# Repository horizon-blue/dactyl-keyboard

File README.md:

# Dactyl Manuform + Trackball with Ergodox layout (sort of)

Disclaimer: I hacked the script for my own use and hard-coded a bunch of meshes. There's no guarantee that the script will work with another layout.

This repo contains yet another fork of Dactyl Manuform that combines [Loligagger's Dactyl Manuform with Ergodox's layout](https://geekhack.org/index.php?topic=88576.msg2852310#msg2852310) with [Wylderbuild's trakball thumb cluster](https://github.com/bullwinkle3000/dactyl-keyboard)

## Changes

- Comparing to the classical Dactyl Manuform model, the "Ergodox layout" has an additional inner column with three keys on each side
- Fixed the strange artifacts that's on the bottom right of Wylderbuild's trakball thumb cluster connector.

- The 1.5U keycaps used to be hanging beyond the case but this should be fixed now.

Pregenerated STL files can be found in the [things](things/) directory

# Wylderbuilds Dactyl Manuform - Python 3 - Cadquery
So, THIS is a fork of a fork of a fork of a... You get the idea.

This one is a direct fork of [joshreve's brilliant adaptation](https://github.com/joshreve/dactyl-keyboard)  of the original Clojure-based dactyl manuform generator redone in Python 3.
Without his work, none of this would have been nearly as easy and straightforward as it has been.  Vast kudos and thanks to him.

This repo is what I've customized and use to generate the models for the prints I sell online at Wylderbuilds, my Etsy store.

## Main Differences and How to Make it Go
Eventually, joshreve and I hope to merge our changes together, but until then, here's a quick rundown on the current changes.

* Wylderbuilds Trackball cluster -- A new, low-rider Trackball cluster. ("thumb_style": "TRACKBALL_WILD")
* Wylderbuilds BTU Trackball cluster -- An even newer Trackball cluster with ball transfer unit support. ("thumb_style": TRACKBALL_BTU")
* 1.5u pinky column support -- Outside 1.5u pinky columns can be generated ("pinky_1_5U": true, "first_1_5U_row": x, "last_1_5U_row": y)
* Full bottom rows -- Default manuforms drop the bottom row keys on outside columns, this keeps them ("full_last_rows": true)
* Clusters broken out into their own classes -- Making it easier to swap among them and add more.
* Updated Kailh Hot swap holder -- If enabled, the hot swap holder is full size and stronger.
* Cadquery builds generate STLs in addition to STEP files -- The bottom plates are (still) only generated properly when the "ENGINE": "cadquery" is set and this will now generate ready-to-print STLs (some models might need a little repair)
* OTHER MISC BITS: OLED mount wall tweaks, tweaks to screw-sizes and some wall placements, manuform angle and heights tweaked, support for an "overrides" json config file.

The main script has been reworked into a single make_dactyl() function.

The setup and run instructions are still more-or-less the same, but here's some tips:

* The docker file likely won't get far, it hasn't been maintained or updated in some time.

* To run locally, the best route is to install Anaconda or Miniconda, start a conda shell and run the "conda.sh" script.  If you're on Windows and don't want to do the WSL Linux thing, you can do the following:

1. Do the Anaconda/Miniconda bit, above.
2. In a conda shell, run the following lines:

        conda create --name=dactyl-keyboard python=3.7 -y

        conda activate dactyl-keyboard

        conda install -c conda-forge -c cadquery cadquery=2 -y

        pip install dataclasses-json numpy scipy solidpython

        conda update --all -y

Then, still in the shell, navigate to the src directory under the repository root and run:

    python dactyl_manuform.py

This will churn and pump out models into the "things" directory.  In run_config.json, "ENGINE": "solid" or "cadquery" will specify OpenSCAD or STEP/STL files, respectively.  Note that the cadquery option takes considerably longer.  Openscad is best for fast iteration.

I'll update more here as things develop.

# The Dactyl-ManuForm Keyboard - Python 3 - Cadquery
This is a fork of [Dactyl-Manuform](https://github.com/tshort/dactyl-keyboard) by Tom Short, which itself is a fork of [Dactyl](https://github.com/adereth/dactyl-keyboard) by Matthew Adereth, a parameterized, split-hand, concave, columnar, ergonomic keyboard.

While the code structure remains comparable to the original, Clojure and OpenSCAD have been replaced by Python and cadquery/OpenCASCADE.  The predecessors were exceptional contributions to the ergo keyboard community by the authors but used a rather esoteric programming language, Clojure, and a relatively inconsistent geometry engine, OpenSCAD.  My hope is that by converting the code the community will have an easier time modifying and evolving this design.  

## Collaborations and Donations
I decided to start accepting donations to help offset some of the prototyping costs and development time.  There are 2 ways to contribute to this project:

### Purchase a kit or keyboard from https://www.ergohaven.xyz/
I am also supported by [ergohaven](https://www.ergohaven.xyz/).  The Dactyl-Manuforms are generated from this repository.  After working with the owner on additions to support new features we decided to collaborate to evolve the designs they can offer and to support my work.  

### Donate directly
I opened Liberapay and Ko-fi accounts to accept donations.  It is obviously not necessary, but is appreciated.  If you do donate and have something specific you really want to see, please let me know. I want to be very open that I can't promise to complete all requests as there are many reasons like engine capabilities and generator construction that can make certain features unfeasible, but I will do my best to improve this repo for you and the ergo keyboard community.

## Helpful Feedback
At this point there has been tons of feedback form the community and I greatly appreciate it.  While I can only work on this in my free time, I do my best to respond to anyone who posts a comment or question.  Feedback on issues or just possible new features is always welcome.

## Updated Geometry Engine, generating STEP files
As part of the effort to create a new engine I converted the code to cadquery/OpenCASCADE.  While OpenSCAD has provided an open source 3D engine that is extremely popular, it frankly creates barely passable STLs when you have complex geometry.  After being extremely frustrated trying to fix the mesh I realized it is just not a stable engine to create high quality files.  OpenCASCADE is extremely powerful but requires extensive detail to operate.  cadquery provided an excellent platform to run a stable geometry engine with a simplified API. 

## Added Features

### Docker Autobuild

At the excellent suggestion of [martint17r](https://github.com/joshreve/dactyl-keyboard/issues?q=is%3Apr+author%3Amartint17r) 
I have added docker configurations with a Windows batch file to assist with getting setup. 
If you have 
[docker desktop](https://www.docker.com/products/docker-desktop) installed, the batch file will create the 
dactyl-keyboard image and 4 containers:

- DM-run: runs `dactyl_manuform.py`, 
- DM-config: runs `generate_configuration.py`
- DM-shell: starts an interactive session to manually run from shell
  - tip: run bash after entering to get a better shell environment
- DM-release-build: runs `model_builder.py` to generate a number of keyboard variants

All apps bindmount the `src` and `things` directory to allow editing in the host and running in the
container.  While not exactly hard drive space efficient, this hopefully helps those having issues getting
cadquery running and prevents local Python conflicts.  It works well on my computer, but I don't use
docker often, so please let me know if you find any issues with the approach.

### Refactored

Your settings are now created by `generate_configuration.py` or by direct modification of the `run_config.json` file.  
This allows you to save `run_config.json` to share your configuration.

Additionally, the OpenSCAD/solid python and OpenCASCADE/cadquery versions are merged with separate helper functions 
to decouple the generator from the target library.  This also lets me stay sane by only modifying one file for most updates.
Running `dactyl_manuform.py` will automatically load the `run_config.json` file. 

### Everyone gets a thumb cluster!

Added support of for the thumb clusters in the [carbonfet Dactyl library](https://github.com/carbonfet/dactyl-manuform).
These are the "mini" and "carbonfet" thumb clusters. Additional trackball cluster added as well more info to be added after additional build and debug time.

Feel free to try them out with by setting `'thumb_style'` to 
`'DEFAULT'`, `'MINI'`, `'CARBONFET'`, `'MINIDOX'`, `'TRACKBALL_ORBYL'`, and `'TRACKBALL_CJ'`.

Trackball features accommodate a [Perixx PERIPRO-303](https://smile.amazon.com/gp/product/B08DD6GQRV/).  Others may fit, but this was the target ball diameter for the design.  It is a little smaller than a Ploopy to try to fit better in the cluster.

Rendered and actual images to be added in future commits.

### Clippable switch mounting

Tired of hot glue and constraining the socket with "nubs"?  I've added an adjustable undercut for using the clips on 
the sockets.  May require some tweaking and little filing, but I have my DM built without any glue and you can too.  
Just use `plate_style = 'UNDERCUT'`.  I've also added an improved local undercut using `plate_style = 'NOTCH'`.

### Kailh Hotswap
Added a new switch for hot swap and a way to include any additional geometry in the key plate by use of an imported file.
For hot swap just use `plate_style = 'HS_NOTCH'`, `plate_style = 'HS_HOLE'`, or `plate_style = 'HS_NUB'`.  
To import an arbitrary geometry set the `plate_file = None` and `plate_offset = 0.0`.  
The file must be .step for OpenCascade / cadquery and .stl for openSCAD / solid python.  
The zero reference should be the key center (XY), and the top of the plate (Z).  
Plate offset is a Z-axis translation for minor adjustments without modifying the geometry file.  

**DISCLAIMER:  I have not built the hot swap version and cannot speak to the geometry.  I found it running around in various places and don't know the origin.  At least one user has claimed it works.**  

If you know the origin I would like to credit the originator.  If you test it I'd love to know how well it works or if you come up with a better geometry I'm happy to add it.  

Message me on Reddit u/j_oshreve if you are really stuck.  I don't have much time to help, but can answer the occasional question.  Also feel free to put in a pull request if you come up with something crafty and want to give others access to it.

### Multiple Controller Mounts

Added an external mount for a separate controller tray.  Looks to work with lolligag's controller trays / holders:

- [Promicro V1](https://dactyl.siskam.link/loligagger-external-holder-promicro-v1.stl)
- [Promicro V2](https://dactyl.siskam.link/loligagger-external-holder-promicro-v2.stl)
- [Elite-C V1 ](https://dactyl.siskam.link/loligagger-external-holder-elite-c-v1.stl)

Just use `controller_mount_type = 'EXTERNAL'`.

This is a new feature so any feedback is appreciated.  If you have issues, message me on Reddit and I will try to help correct them.

### OLED Display Mount

Added 3 OLED mounts.  Have printed them stand alone with success.  I suggest clip, but it may require some tweaks based on your printer (over vs under sized).

`oled_mount_type = 'CLIP'` creates an opening to set the OLED with a clip on face plate to hold it down.  This is the preferred mounting, but needs the OLED to have a removable connection.  

`oled_mount_type = 'SLIDING'` creates an opening such that you can slide the screen up through the back and into place.  Needs a piece of foam or a bit of glue to lock in place.

`oled_mount_type = 'UNDERCUT'` creates an opening with an undercut to create whatever custom holder you want.  Will not work without additional part creation from the user.

This is a new feature so any feedback is appreciated.  If you have issues, message me on Reddit and I will try to help correct them.  

### Screw Post Locations

You can now have slightly better control of screw mounts.  Set to `'screws_offset':'INSIDE'`, `'screws_offset':'OUTSIDE'` or `'screws_offset': 'ORIGINAL'` to control screw locations relative to the wall. 

I am planning to deprecate outside and original at some point.  I don't see the need to carry all of them and the hidden look the best.  If you disagree feel free to let me know and I may keep a second form.

## Status / Future
This is now a bit of a monster of many minds and yet continues to bear fruit.  
I plan to continue to use this code to try new geometries and features to share for the foreseeable future.

## Installation

There are three different environments in which you can run this application. Depending on which you choose, the installation process will vary.

- [Docker Environment](#docker-environment-installation)
- [Conda Environment](#conda-environment-installation)
- [Python Environment](#python-environment-installation)

### Docker Environment Installation

Running the application with Docker is the most convenient way to do so. In addition to a straightforward installation, this also allows you to generate models in the background without having to keep a shell open.

*Note:* If you are using Windows, see [Docker Autobuild](#docker-autobuild).

Before you proceed, ensure you have installed [Docker](https://www.docker.com/) and the `docker` command is available from your terminal.

There are two tools you can use to help manage the Docker containers associated with this project. 

#### Make

If you prefer, you can use `make` to manage the containers. Type `make help` to see the available commands.

#### Bash Script

The `dactyl.sh` bash script provides a CLI to manage the containers. Type `./dactyl.sh --help` to see all CLI options.

In addition to the CLI you can run `./dactyl.sh` without any arguments to use an interactive menu. 

Upon running the script, you will be prompted to build the dactyl-keyboard Docker image.

Once the image is built, you can choose which containers to run on an as-needed basis. In general, you can start, stop, rebuild, inspect, and remove the containers via the CLI/Menu. 

You can also remove all of the Docker artifacts by running the included uninstaller.

*Tip:* Run `./dactyl.sh shell --session` to jump into a bash session inside of the shell container.

### Conda Environment Installation

After the Docker installation, Anaconda is the next best option. Before you begin, ensure you have installed [Anaconda](https://docs.anaconda.com/anaconda/install/index.html) and the `conda` command is available from your terminal.

You can install all of the dependencies by hand, but you can automate the install by running the bash script `./conda.sh`. This will create a python 3.7 environment named `dactyl-keyboard` and install all of the required dependencies.

If you would like to install into a conda environment manually, check the bash script to see all of the required commands.

If you would like to remove the conda artifacts, run `./conda.sh --uninstall`.

### Python Environment Installation

You can install the application in a regular python environment, but it is not recommended. You will not be able to take advantage of the updated geometry generated by the CadQuery engine, as this is only available via the Docker/Anaconda installation.

**Setting up the Python environment - NEW**
* [Install Python 3.X](https://www.python.org/downloads/release/python-385/) or use your [favorite distro / platform (Anaconda)](https://www.anaconda.com/products/individual) 
* It is advisable, but not necessary, to setup a virtual environment to prevent package/library incompatibility 
* [Install Numpy](https://pypi.org/project/numpy/), easiest method is `pip install numpy` or `pip3 install numpy` on linux.
* [Install dataclasses_json](https://pypi.org/project/dataclasses_json/), easiest method is `pip install dataclasses-json` or `pip3 install dataclasses-json` on linux.

**cadquery install**
* [Install scipy](https://pypi.org/project/scipy/), easiest method is `pip install scipy` or `pip3 install scipy` on linux.
* [Install cadquery](https://github.com/CadQuery/cadquery), many options (see link), but easiest method is `conda install -c conda-forge -c cadquery cadquery=2`.  Props to the creators/maintainers, this has the power of Open CASCADE with nearing the simplicity of OpenSCAD.

**OpenSCAD install**
* [Install SolidPython](https://pypi.org/project/solidpython/), easiest method is `pip install solidpython` or `pip3 install solidpython` on linux.
* [Install OpenSCAD](http://www.openscad.org/)

## Generating the design

**Generating the design - UPDATED**
* ~~Run `python dactyl_manuform_cadquery.py` or `python3 dactyl_manuform_cadquery.py`~~ 
* ~~Run `python dactyl_manuform.py` or `python3 dactyl_manuform.py`~~
* Run `generate_configuration.py` or directly edit `run_config.json` to configure the design
* Run `dactyl_manuform.py` to create the geometry (ENGINE variable in run determines method)
* This will regenerate the `things/` files (or in subdirectory if defined in config)
    * `*left.*`
    * `*right.*`
    * `*plate.*`
    * `*oled_clip.*` (if applicable)
    * `*oled_clip_test.*` (if applicable)
* Use OpenSCAD to open a `.scad` file
* Use FreeCAD or other application to open a `.step` file
* Make changes to design, repeat run step
* When done, use OpenSCAD or FreeCAD to export STL files

**The majority of the the rest of the below content is as defined by previous authors, except where noted.**

## Origin

The main change is that the thumb cluster was adapted from the [ManuForm keyboard](https://github.com/jeffgran/ManuForm) ([geekhack](https://geekhack.org/index.php?topic=46015.0)). The walls were changed to just drop to the floor. The keyboard is paramaterized to allow adjusting the following: 

* Rows: 4 - 6 
* Columns: 5 and up
* Row curvature
* Column curvature
* Row tilt (tenting)
* Column tilt
* Column offsets
* Height

## Assembly

### Printing
Pre-generated files can be opened in OpenSCAD or FreeCAD and exported to STL.  Bottom plate is available as a step file or dxf for cadquery or a .scad file to be exported from OpenSCAD.

### Wiring

Here are materials tshort used for wiring.

* Two Arduino Pro Micros
* [Heat-set inserts](https://www.mcmaster.com/#94180a331/=16yfrx1)
* [M3 wafer-head screws, 5mm](http://www.metricscrews.us/index.php?main_page=product_info&cPath=155_185&products_id=455)
* [Copper tape](https://www.amazon.com/gp/product/B009KB86BU)
* [#32 magnet wire](https://www.amazon.com/gp/product/B00LV909HI)
* [#30 wire](https://www.amazon.com/gp/product/B00GWFECWO)
* [3-mm cast acrylic](http://www.mcmaster.com/#acrylic/=144mfom)
* [Veroboard stripboard](https://www.amazon.com/gp/product/B008CPVMMU)
* [1N4148 diodes](https://www.amazon.com/gp/product/B00LQPY0Y0)
* [Female RJ-9 connectors](https://www.amazon.com/gp/product/B01HU7BVDU/)

I wired one half using the traditional approach of using the legs of a diode to form the row connections. 
(I'm not great at soldering, so this was challenging for me.)
For this side, I used magnet wire to wire columns. That worked okay. 
The magnet wire is small enough, it wants to move around, and it's hard to tell if you have a good connection.

For another half, I used stripboard for the row connections. 
This allowed me to presolder all of the diodes. 
Then, I hot-glued this in place and finished the soldering of the other diode ends. 
I like this approach quite a lot. 
Connections for the diodes were much easier with one end fixed down. 
On this half, I also used copper tape to connect columns. 
This worked a bit better than the magnet wire for me. 
For a future version, I may try just bare tinned copper wire for columns (something like #20). 
With the stripboard, it's pretty easy keeping row and column connections separate.

Note that a telephone handset cable has leads that are reversed, so take this into account when connecting these leads to the controller.

The 3D printed part is the main keyboard. 
You can attach a bottom plate with screws. 
The case has holes for heat-set inserts designed to hold 3- to 6-mm long M3 screws. 
Then, I used wafer-head screws to connect a bottom plate. 
If wires aren't dangling, a bottom plate may not be needed. 
You need something on the bottom to keep the keyboard from sliding around. 
Without a plate, you could use a rubber pad, or you could dip the bottom of the keyboard in PlastiDip.

For more photos of the first complete wiring of v0.4, see [Imgur](http://imgur.com/a/v9eIO).

This is how the rows/columns wire to the keys and the ProMicro

#### Alternative row-driven wiring diagram for ProMicro:

NOTE: you also make sure the firmware is set up correctly (ex: change row pins with col pins)

### Firmware

Firmware goes hand in hand with how you wire the circuit. 
I adapted the QMK firmware [here](https://github.com/tshort/qmk_firmware/tree/master/keyboards/dactyl-manuform). 
This allows each side to work separately or together. 
This site also shows connections for the Arduino Pro Micro controllers.

## License

General Code Copyright © 2015-2021 Matthew Adereth, Tom Short, and Joshua Shreve
Mini thumb cluster Copyright © 2015-2018 Matthew Adereth, Tom Short, and Leo Lou
Carbonfet thumb cluster © 2015-2018 Matthew Adereth, Tom Short, and carbonfet (github username)

The source code for generating the models (everything excluding the [things/](things/) and [resources/](resources/) directories is distributed under the [GNU AFFERO GENERAL PUBLIC LICENSE Version 3](LICENSE).  The generated models and PCB designs are distributed under the [Creative Commons Attribution-NonCommercial-ShareAlike License Version 3.0](LICENSE-models).

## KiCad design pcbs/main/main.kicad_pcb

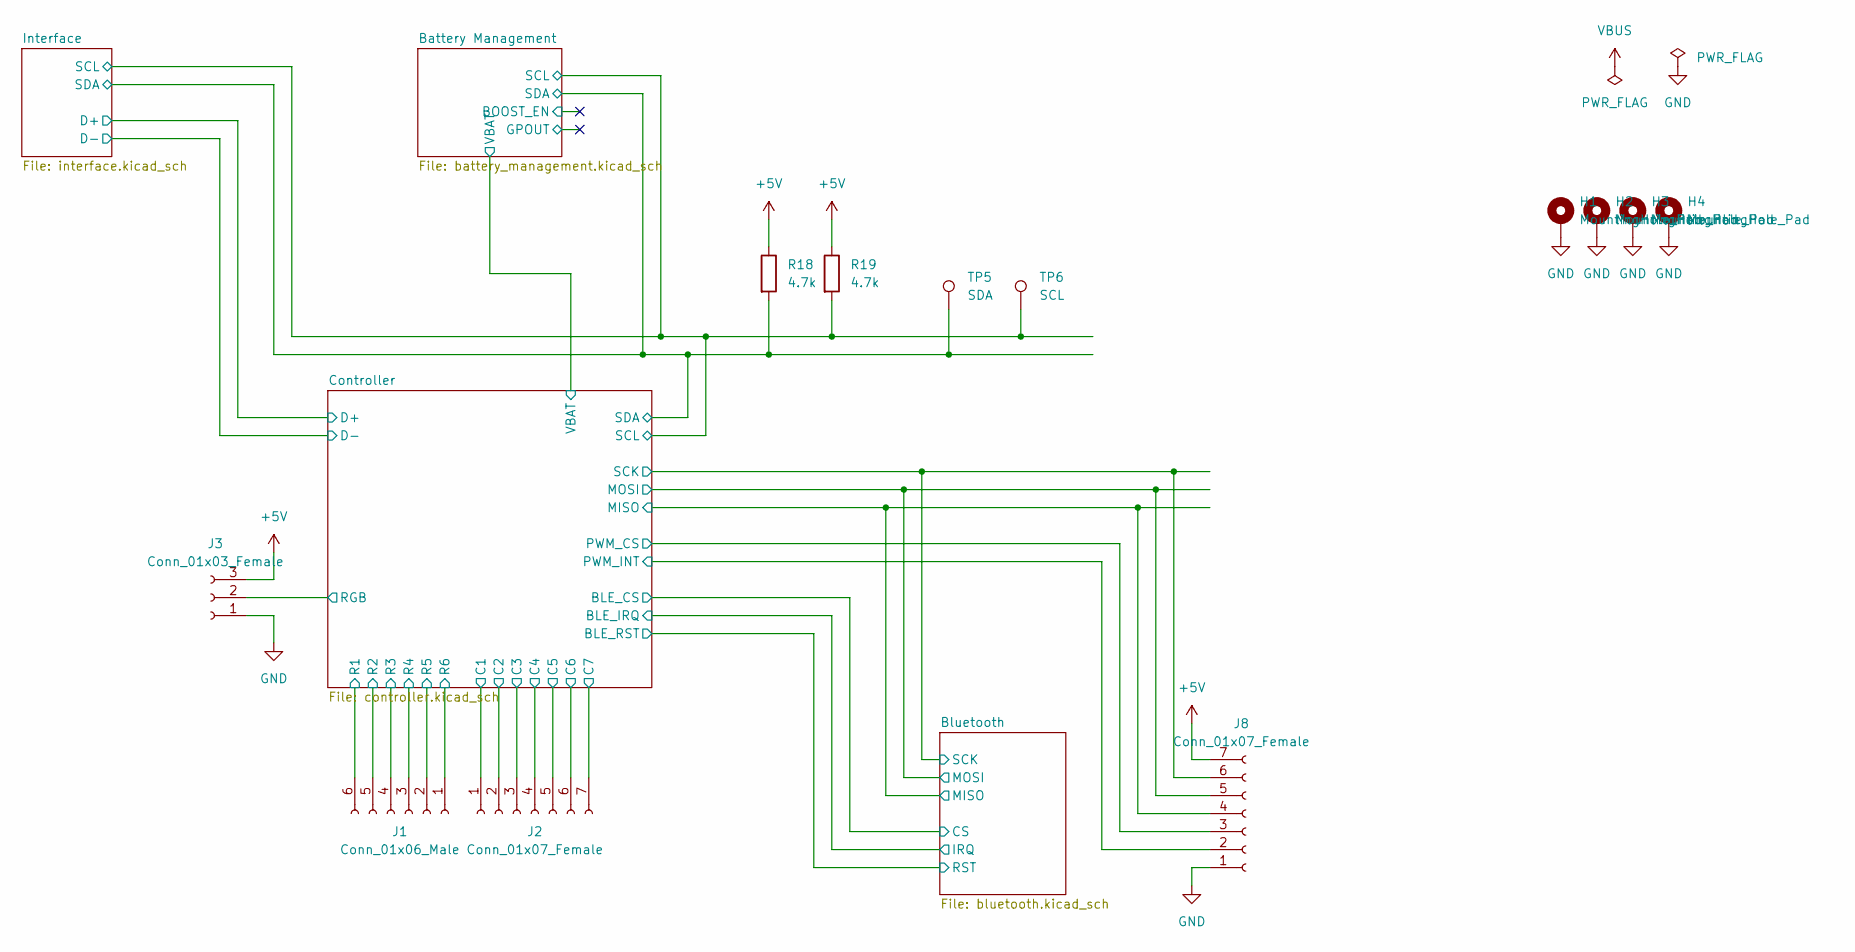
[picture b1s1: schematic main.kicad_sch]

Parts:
H1, H2, H3, H4: MountingHole_Pad; MountingHole_2.2mm_M2_Pad_Via
J1: Conn_01x06_Male; JST_PH_B6B-PH-K_1x06_P2.00mm_Vertical
J2, J8: Conn_01x07_Female; JST_PH_B7B-PH-K_1x07_P2.00mm_Vertical
J3: Conn_01x03_Female; JST_PH_B3B-PH-K_1x03_P2.00mm_Vertical
R18, R19: 4.7k; R_0603_1608Metric
TP5: SDA; TestPoint_Keystone_5019_Minature
TP6: SCL; TestPoint_Keystone_5019_Minature

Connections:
+5V: J3.3, J8.7, R18.1, R19.1; also elsewhere on the board
/Battery Management/SCL: R19.2, TP6.1; also elsewhere on the board
/Battery Management/SDA: R18.2, TP5.1; also elsewhere on the board
/Bluetooth/MISO: J8.4; also elsewhere on the board
/Bluetooth/MOSI: J8.5; also elsewhere on the board
/Bluetooth/SCK: J8.6; also elsewhere on the board
/Controller/C1: J2.1; also elsewhere on the board
/Controller/C2: J2.2; also elsewhere on the board
/Controller/C3: J2.3; also elsewhere on the board
/Controller/C4: J2.4; also elsewhere on the board
/Controller/C5: J2.5; also elsewhere on the board
/Controller/C6: J2.6; also elsewhere on the board
/Controller/C7: J2.7; also elsewhere on the board
/Controller/PWM_CS: J8.3; also elsewhere on the board
/Controller/PWM_INT: J8.2; also elsewhere on the board
/Controller/R1: J1.6; also elsewhere on the board
/Controller/R2: J1.5; also elsewhere on the board
/Controller/R3: J1.4; also elsewhere on the board
/Controller/R4: J1.3; also elsewhere on the board
/Controller/R5: J1.2; also elsewhere on the board
/Controller/R6: J1.1; also elsewhere on the board
/Controller/RGB: J3.2; also elsewhere on the board
GND: H1.1, H2.1, H3.1, H4.1, J3.1, J8.1; also elsewhere on the board

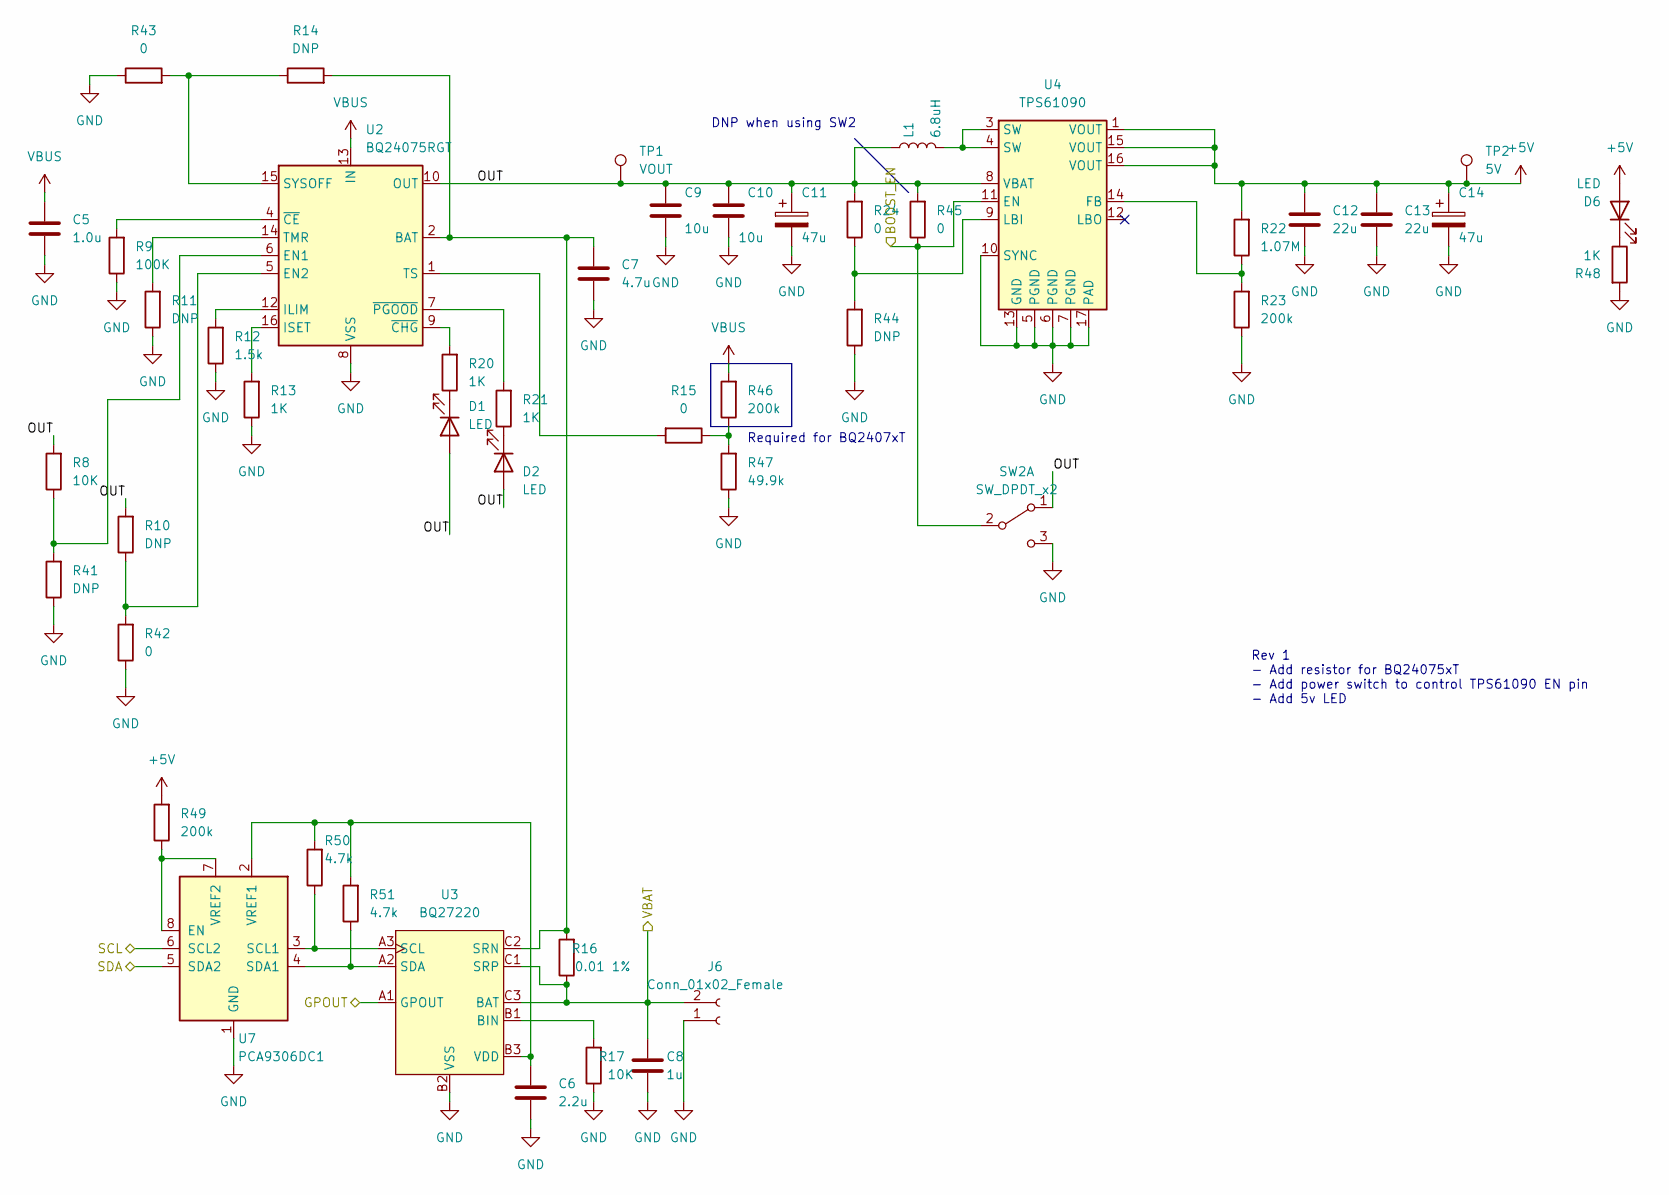
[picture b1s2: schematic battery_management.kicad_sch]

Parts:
C5: 1.0u; C_0603_1608Metric
C6: 2.2u; C_0603_1608Metric
C7: 4.7u; C_0603_1608Metric
C8: 1u; C_0603_1608Metric
C9, C10: 10u; C_0805_2012Metric
C11, C14: 47u; CP_EIA-3216-18_Kemet-A
C12, C13: 22u; C_0805_2012Metric
D1, D2, D6: LED; LED_0603_1608Metric
J6: Conn_01x02_Female; JST_PH_B2B-PH-K_1x02_P2.00mm_Vertical
L1: 6.8uH; L_Taiyo-Yuden_NR-80xx_HandSoldering
R8, R17: 10K; R_0603_1608Metric
R9: 100K; R_0603_1608Metric
R10, R11, R14, R41, R44: DNP; R_0603_1608Metric
R12: 1.5k; R_0603_1608Metric
R13, R20, R21, R48: 1K; R_0603_1608Metric
R15, R24, R42, R43, R45: 0; R_0603_1608Metric
R16: 0.01 1%; R_2512_6332Metric
R22: 1.07M; R_0603_1608Metric
R23, R46, R49: 200k; R_0603_1608Metric
R47: 49.9k; R_0603_1608Metric
R50, R51: 4.7k; R_0603_1608Metric
SW2: SW_DPDT_x2; SW_DPDT_CK_JS202011JCQN
TP1: VOUT; TestPoint_Keystone_5019_Minature
TP2: 5V; TestPoint_Keystone_5019_Minature
U2: BQ24075RGT; VQFN-16-1EP_3x3mm_P0.5mm_EP1.6x1.6mm
U3: BQ27220; Texas_DSBGA-9_1.4715x1.4715mm_Layout3x3_P0.5mm
U4: TPS61090; Texas_S-PVQFN-N16_EP2.7x2.7mm
U7: PCA9306DC1; VSSOP-8_2.3x2mm_P0.5mm

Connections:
+5V: C12.1, C13.1, C14.1, D6.2 (A), R22.2, R49.2, TP2.1, U4.1 (VOUT), U4.15 (VOUT), U4.16 (VOUT); also elsewhere on the board
/Battery Management/BOOST_EN: R45.1, SW2.2 (B), U4.11 (EN)
/Battery Management/GPOUT: U3.A1 (GPOUT)
/Battery Management/OUT: C9.1, C10.1, C11.1, D1.2 (A), D2.2 (A), L1.1, R8.2, R10.2, R24.2, R45.2, SW2.1 (A), TP1.1, U2.10 (OUT), U2.11 (OUT), U4.8 (VBAT)
/Battery Management/SCL: U7.6 (SCL2); also elsewhere on the board
/Battery Management/SDA: U7.5 (SDA2); also elsewhere on the board
/Battery Management/VBAT: C8.1, J6.2, R16.1, U3.C1 (SRP), U3.C3 (BAT); also elsewhere on the board
GND: C5.2, C6.2, C7.2, C8.2, C9.2, C10.2, C11.2, C12.2, C13.2, C14.2, J6.1, R9.1, R11.1, R12.1, R13.1, R17.1, R23.1, R41.1, R42.1, R43.1, R44.1, R47.1, R48.2, SW2.3 (C), U2.8 (VSS), U2.17 (VSS), U3.B2 (VSS), U4.5 (PGND), U4.6 (PGND), U4.7 (PGND), U4.10 (SYNC), U4.13 (GND), U4.17 (PAD), U7.1 (GND); also elsewhere on the board
unnamed: C6.1, R50.2, R51.2, U3.B3 (VDD), U7.2 (VREF1)
unnamed: C7.1, R14.2, R16.2, U2.2 (BAT), U2.3 (BAT), U3.C2 (SRN)
unnamed: D1.1 (K), R20.1
unnamed: D2.1 (K), R21.1
unnamed: D6.1 (K), R48.1
unnamed: L1.2, U4.3 (SW), U4.4 (SW)
unnamed: R9.2, U2.4 (~CE)
unnamed: R10.1, R42.2, U2.5 (EN2)
unnamed: R11.2, U2.14 (TMR)
unnamed: R12.2, U2.12 (ILIM)
unnamed: R13.2, U2.16 (ISET)
unnamed: R14.1, R43.2, U2.15 (SYSOFF)
unnamed: R15.1, R46.1, R47.2
unnamed: R15.2, U2.1 (TS)
unnamed: R17.2, U3.B1 (BIN)
unnamed: R20.2, U2.9 (~CHG)
unnamed: R21.2, U2.7 (~PGOOD)
unnamed: R22.1, R23.2, U4.14 (FB)
unnamed: R24.1, R44.2, U4.9 (LBI)
unnamed: R8.1, R41.2, U2.6 (EN1)
unnamed: R49.1, U7.7 (VREF2), U7.8 (EN)
unnamed: R50.1, U3.A3 (SCL), U7.3 (SCL1)
unnamed: R51.1, U3.A2 (SDA), U7.4 (SDA1)
VBUS: C5.1, R46.2, U2.13 (IN); also elsewhere on the board

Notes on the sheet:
DNP when using SW2
Required for BQ2407xT
Rev 1 - Add resistor for BQ24075xT - Add power switch to control TPS61090 EN pin - Add 5v LED

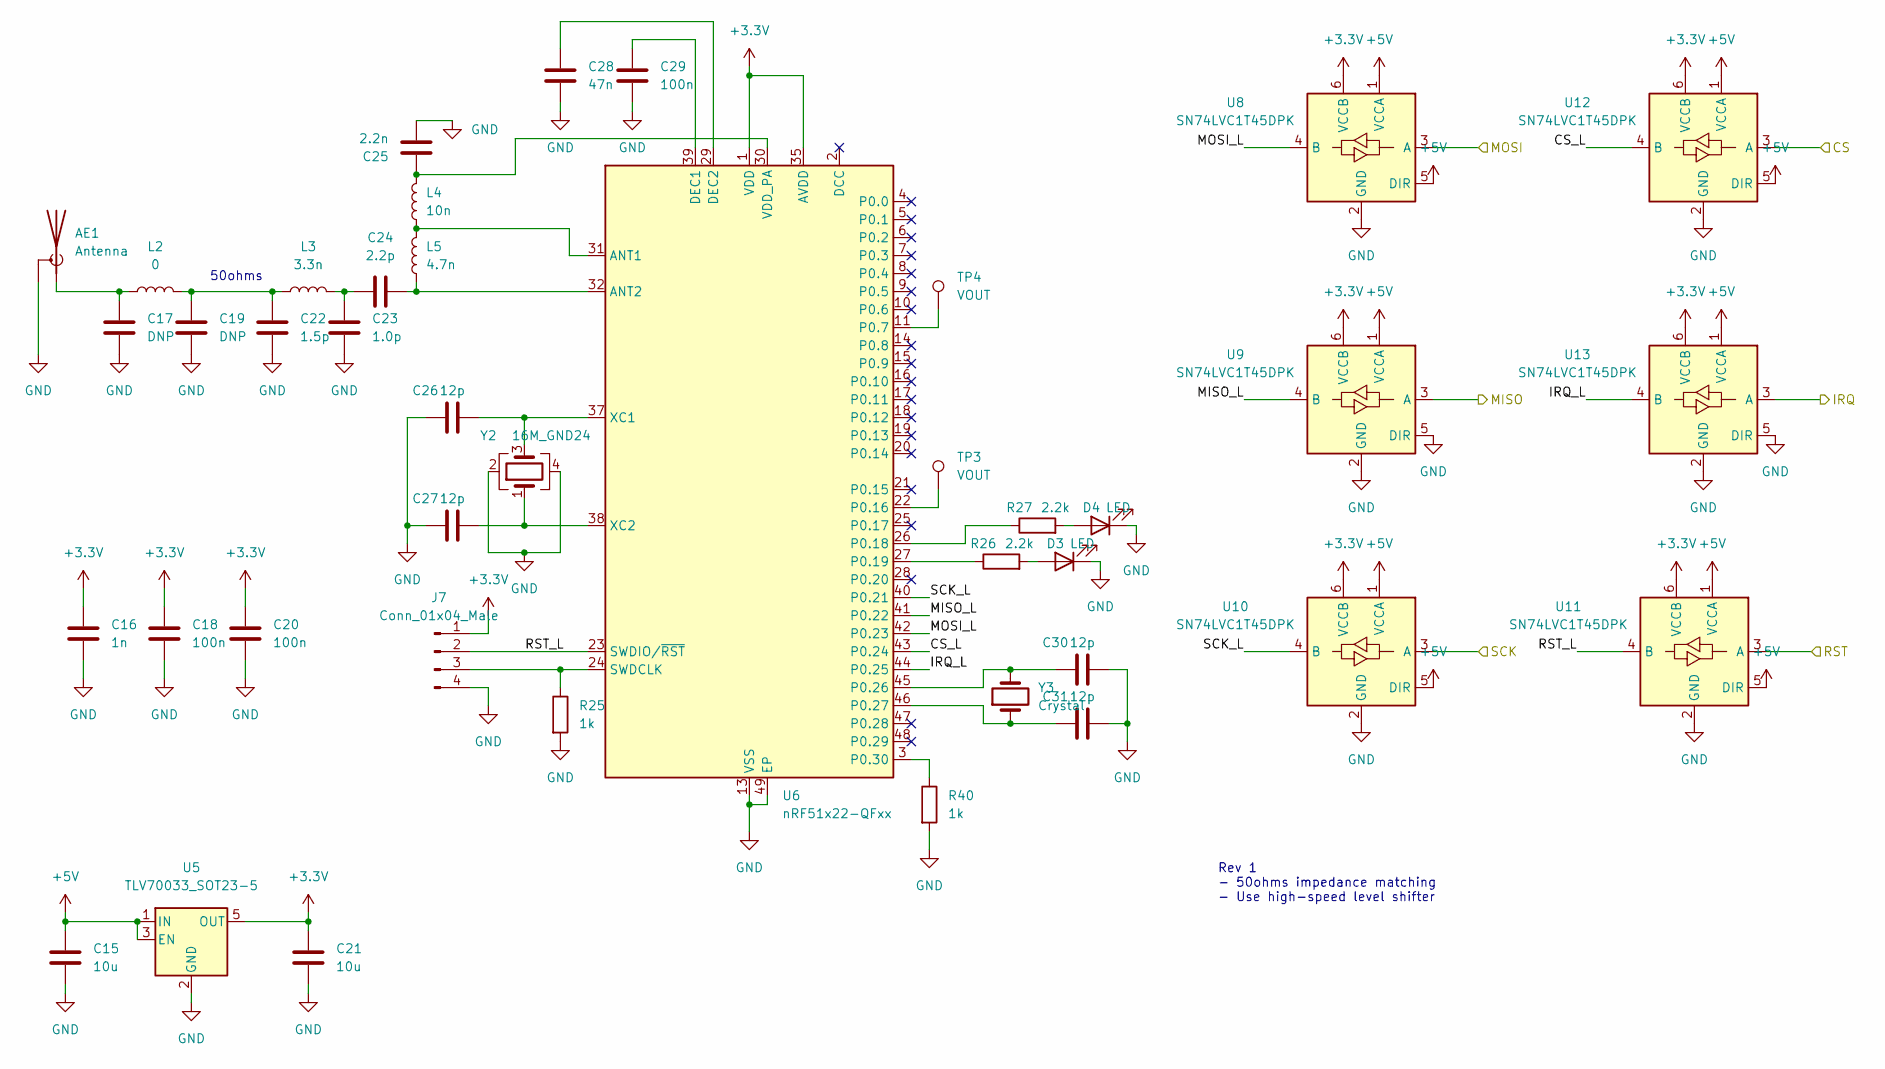
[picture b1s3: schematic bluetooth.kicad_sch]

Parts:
AE1: Antenna; Texas_SWRA117D_2.4GHz_Right
C15, C21: 10u; C_0603_1608Metric
C16: 1n; C_0603_1608Metric
C17, C19: DNP; C_0402_1005Metric
C18, C20, C29: 100n; C_0603_1608Metric
C22: 1.5p; C_0402_1005Metric
C23: 1.0p; C_0402_1005Metric
C24: 2.2p; C_0402_1005Metric
C25: 2.2n; C_0402_1005Metric
C26, C27, C30, C31: 12p; C_0603_1608Metric
C28: 47n; C_0603_1608Metric
D3, D4: LED; LED_0603_1608Metric
J7: Conn_01x04_Male; PinHeader_1x04_P2.54mm_Vertical
L2: 0; L_0402_1005Metric
L3: 3.3n; L_0402_1005Metric
L4: 10n; L_0402_1005Metric
L5: 4.7n; L_0402_1005Metric
R25, R40: 1k; R_0603_1608Metric
R26, R27: 2.2k; R_0603_1608Metric
TP3, TP4: VOUT; TestPoint_Keystone_5019_Minature
U5: TLV70033_SOT23-5; SOT-23-5
U6: nRF51x22-QFxx; QFN-48-1EP_6x6mm_P0.4mm_EP4.6x4.6mm
U8, U9, U10, U11, U12, U13: SN74LVC1T45DPK; USON-6
Y2: 16M_GND24; Crystal_SMD_2016-4Pin_2.0x1.6mm; LCSC Part# C431146
Y3: Crystal; Crystal_SMD_3215-2Pin_3.2x1.5mm

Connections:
+3V3: C16.1, C18.1, C20.1, C21.1, J7.1, U5.5 (OUT), U6.1 (VDD), U6.12 (VDD), U6.35 (AVDD), U6.36 (AVDD), U8.6 (VCCB), U9.6 (VCCB), U10.6 (VCCB), U11.6 (VCCB), U12.6 (VCCB), U13.6 (VCCB)
+5V: C15.1, U5.1 (IN), U5.3 (EN), U8.1 (VCCA), U8.5 (DIR), U9.1 (VCCA), U10.1 (VCCA), U10.5 (DIR), U11.1 (VCCA), U11.5 (DIR), U12.1 (VCCA), U12.5 (DIR), U13.1 (VCCA); also elsewhere on the board
/Bluetooth/CS: U12.3 (A); also elsewhere on the board
/Bluetooth/CS_L: U6.43 (P0.24), U12.4 (B)
/Bluetooth/IRQ: U13.3 (A); also elsewhere on the board
/Bluetooth/IRQ_L: U6.44 (P0.25), U13.4 (B)
/Bluetooth/MISO: U9.3 (A); also elsewhere on the board
/Bluetooth/MISO_L: U6.41 (P0.22), U9.4 (B)
/Bluetooth/MOSI: U8.3 (A); also elsewhere on the board
/Bluetooth/MOSI_L: U6.42 (P0.23), U8.4 (B)
/Bluetooth/RST: U11.3 (A); also elsewhere on the board
/Bluetooth/RST_L: J7.2, U6.23 (SWDIO/~RST), U11.4 (B)
/Bluetooth/SCK: U10.3 (A); also elsewhere on the board
/Bluetooth/SCK_L: U6.40 (P0.21), U10.4 (B)
GND: AE1.2 (Shield), C15.2, C16.2, C17.1, C18.2, C19.1, C20.2, C21.2, C22.1, C23.1, C25.2, C26.1, C27.1, C28.2, C29.2, C30.2, C31.2, D3.1 (K), D4.1 (K), J7.4, R25.2, R40.2, U5.2 (GND), U6.13 (VSS), U6.33 (VSS), U6.34 (VSS), U6.49 (EP), U8.2 (GND), U9.2 (GND), U9.5 (DIR), U10.2 (GND), U11.2 (GND), U12.2 (GND), U13.2 (GND), U13.5 (DIR), Y2.2, Y2.4; also elsewhere on the board
unnamed: AE1.1 (A), C17.2, L2.1
unnamed: C19.2, C22.2, L2.2, L3.1
unnamed: C23.2, C24.1, L3.2
unnamed: C24.2, L5.1, U6.32 (ANT2)
unnamed: C25.1, L4.2, U6.30 (VDD_PA)
unnamed: C26.2, U6.37 (XC1), Y2.3
unnamed: C27.2, U6.38 (XC2), Y2.1
unnamed: C28.1, U6.29 (DEC2)
unnamed: C29.1, U6.39 (DEC1)
unnamed: C30.1, U6.45 (P0.26), Y3.2
unnamed: C31.1, U6.46 (P0.27), Y3.1
unnamed: D3.2 (A), R26.2
unnamed: D4.2 (A), R27.2
unnamed: J7.3, R25.1, U6.24 (SWDCLK)
unnamed: L4.1, L5.2, U6.31 (ANT1)
unnamed: R26.1, U6.27 (P0.19)
unnamed: R27.1, U6.26 (P0.18)
unnamed: R40.1, U6.3 (P0.30)
unnamed: TP3.1, U6.22 (P0.16)
unnamed: TP4.1, U6.11 (P0.7)

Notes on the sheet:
Rev 1 - 50ohms impedance matching - Use high-speed level shifter
50ohms

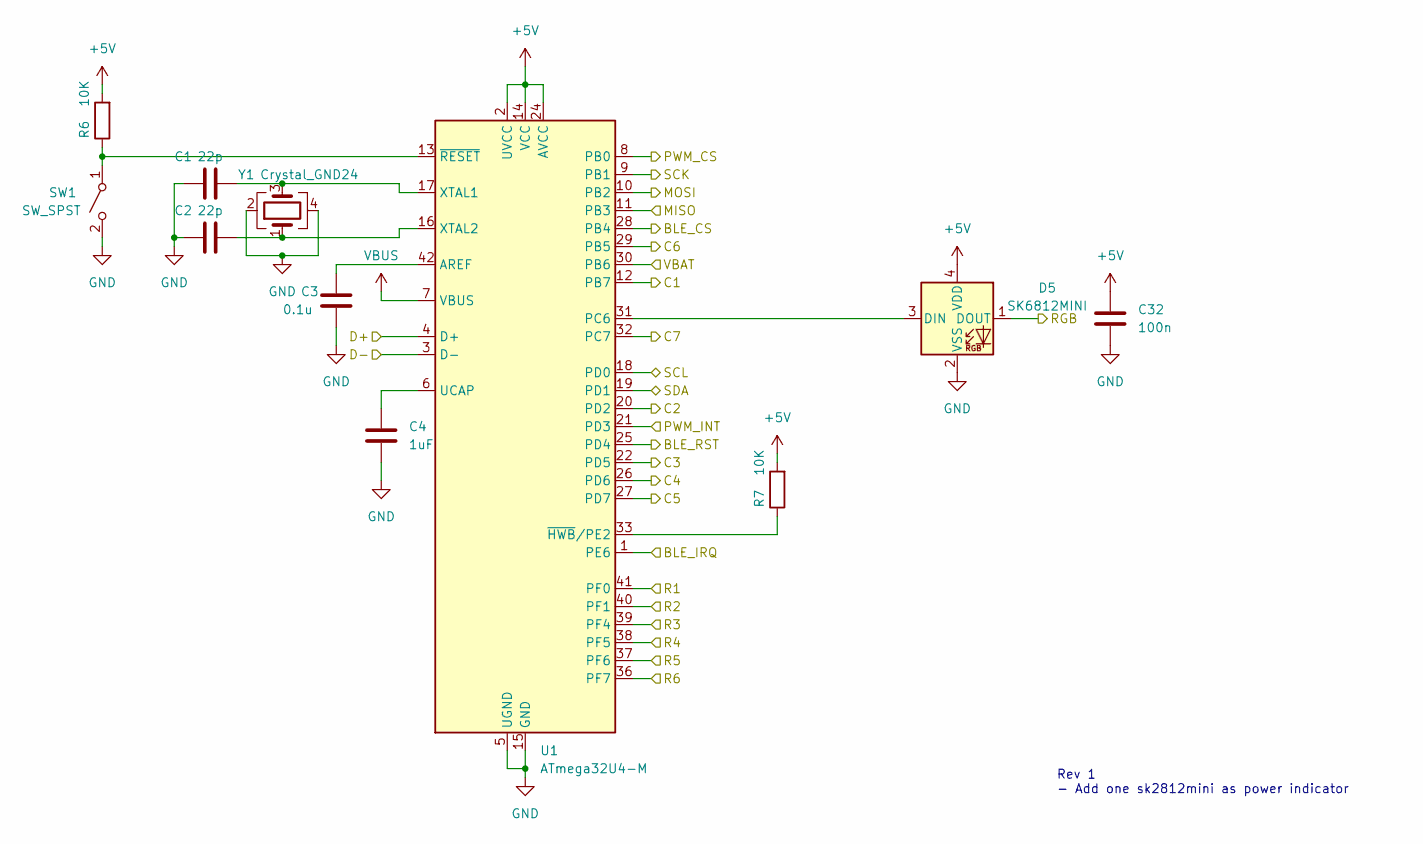
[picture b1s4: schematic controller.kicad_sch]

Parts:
C1, C2: 22p; C_0603_1608Metric
C3: 0.1u; C_0603_1608Metric
C4: 1uF; C_0603_1608Metric
C32: 100n; C_0603_1608Metric
D5: SK6812MINI; LED_SK6812MINI_PLCC4_3.5x3.5mm_P1.75mm
R6, R7: 10K; R_0603_1608Metric
SW1: SW_SPST; SW_SPST_EVQP7C; LCSC Part# C388883
U1: ATmega32U4-M; QFN-44-1EP_7x7mm_P0.5mm_EP5.2x5.2mm
Y1: Crystal_GND24; Crystal_SMD_2016-4Pin_2.0x1.6mm; LCSC Part# C431146

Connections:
+5V: C32.1, D5.4 (VDD), R6.2, R7.2, U1.2 (UVCC), U1.14 (VCC), U1.24 (AVCC), U1.34 (VCC), U1.44 (AVCC); also elsewhere on the board
/Battery Management/SCL: U1.18 (PD0); also elsewhere on the board
/Battery Management/SDA: U1.19 (PD1); also elsewhere on the board
/Battery Management/VBAT: U1.30 (PB6); also elsewhere on the board
/Bluetooth/CS: U1.28 (PB4); also elsewhere on the board
/Bluetooth/IRQ: U1.1 (PE6); also elsewhere on the board
/Bluetooth/MISO: U1.11 (PB3); also elsewhere on the board
/Bluetooth/MOSI: U1.10 (PB2); also elsewhere on the board
/Bluetooth/RST: U1.25 (PD4); also elsewhere on the board
/Bluetooth/SCK: U1.9 (PB1); also elsewhere on the board
/Controller/C1: U1.12 (PB7); also elsewhere on the board
/Controller/C2: U1.20 (PD2); also elsewhere on the board
/Controller/C3: U1.22 (PD5); also elsewhere on the board
/Controller/C4: U1.26 (PD6); also elsewhere on the board
/Controller/C5: U1.27 (PD7); also elsewhere on the board
/Controller/C6: U1.29 (PB5); also elsewhere on the board
/Controller/C7: U1.32 (PC7); also elsewhere on the board
/Controller/D+: U1.4 (D+); also elsewhere on the board
/Controller/D-: U1.3 (D-); also elsewhere on the board
/Controller/PWM_CS: U1.8 (PB0); also elsewhere on the board
/Controller/PWM_INT: U1.21 (PD3); also elsewhere on the board
/Controller/R1: U1.41 (PF0); also elsewhere on the board
/Controller/R2: U1.40 (PF1); also elsewhere on the board
/Controller/R3: U1.39 (PF4); also elsewhere on the board
/Controller/R4: U1.38 (PF5); also elsewhere on the board
/Controller/R5: U1.37 (PF6); also elsewhere on the board
/Controller/R6: U1.36 (PF7); also elsewhere on the board
/Controller/RGB: D5.1 (DOUT); also elsewhere on the board
GND: C1.1, C2.1, C3.2, C4.2, C32.2, D5.2 (VSS), SW1.2 (B), U1.5 (UGND), U1.15 (GND), U1.23 (GND), U1.35 (GND), U1.43 (GND), U1.45 (GND), Y1.2, Y1.4; also elsewhere on the board
unnamed: C1.2, U1.17 (XTAL1), Y1.3
unnamed: C2.2, U1.16 (XTAL2), Y1.1
unnamed: C3.1, U1.42 (AREF)
unnamed: C4.1, U1.6 (UCAP)
unnamed: D5.3 (DIN), U1.31 (PC6)
unnamed: R6.1, SW1.1 (A), U1.13 (~RESET)
unnamed: R7.1, U1.33 (~HWB/PE2)
VBUS: U1.7 (VBUS); also elsewhere on the board

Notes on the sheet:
Rev 1 - Add one sk2812mini as power indicator

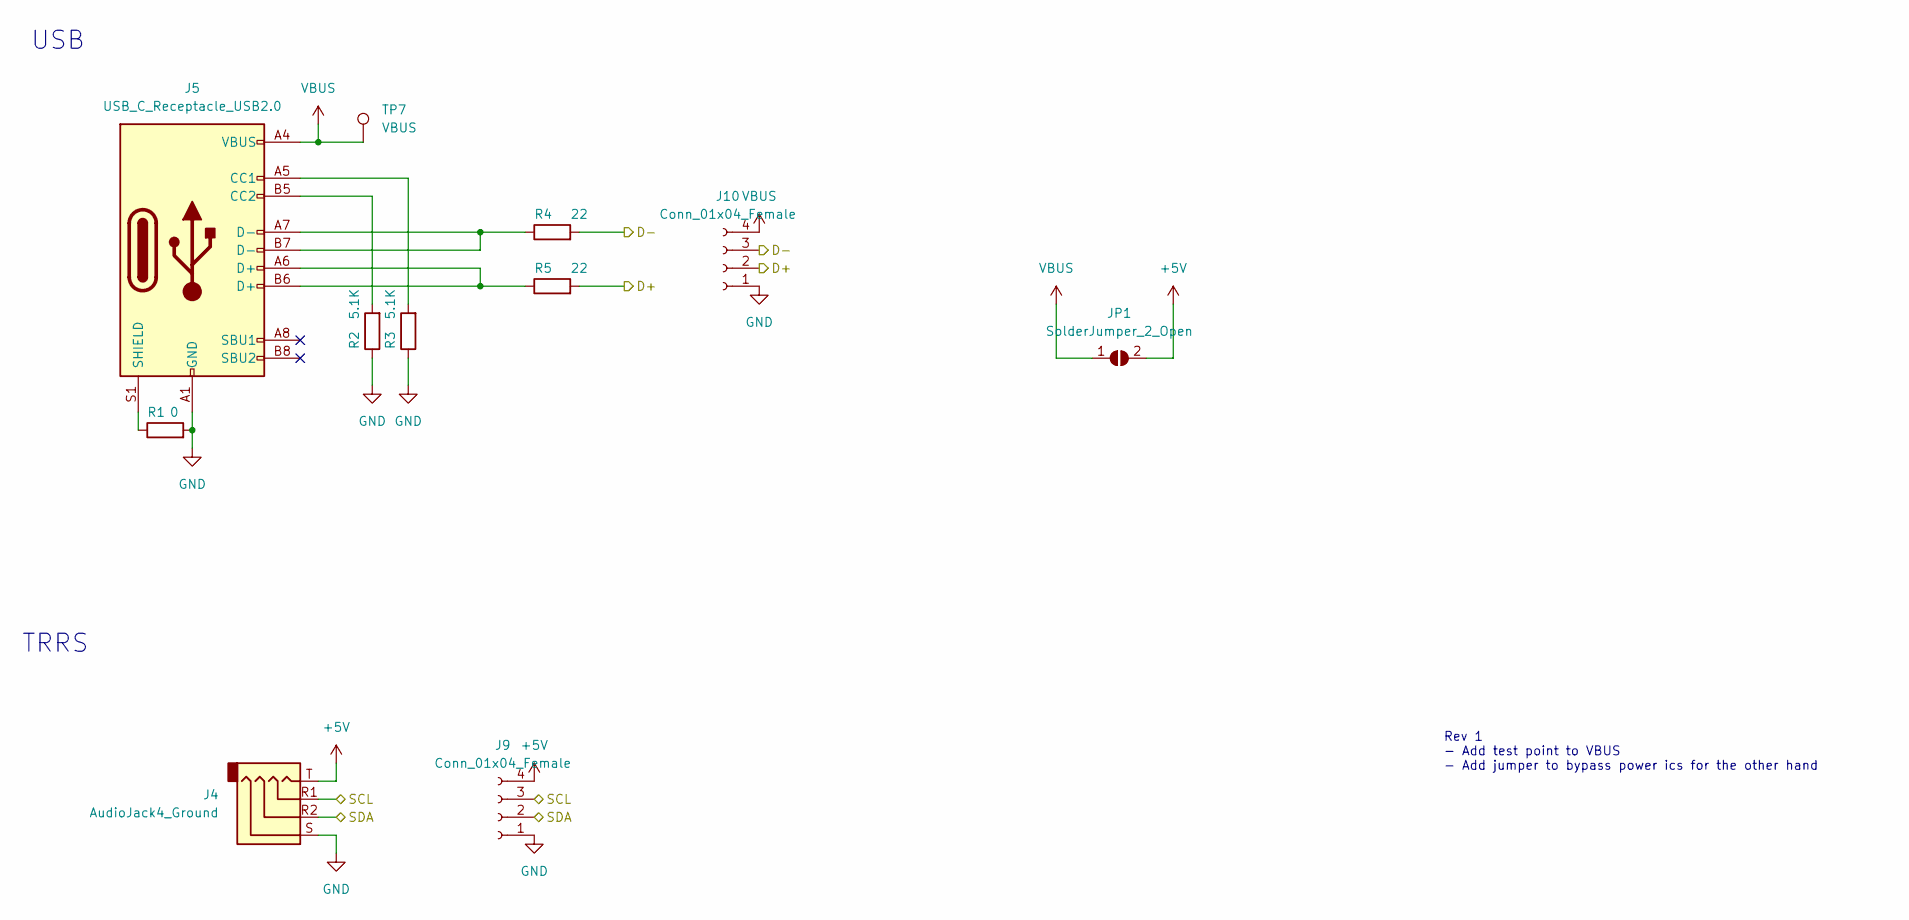
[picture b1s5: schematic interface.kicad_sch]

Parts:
J4: AudioJack4_Ground; Jack_3.5mm_PJ320D_Horizontal
J5: USB_C_Receptacle_USB2.0; USB_C_Receptacle_XKB_U262-16XN-4BVC11
J9, J10: Conn_01x04_Female; JST_PH_B4B-PH-K_1x04_P2.00mm_Vertical
JP1: SolderJumper_2_Open; SolderJumper-2_P1.3mm_Open_TrianglePad1.0x1.5mm
R1: 0; R_0603_1608Metric
R2, R3: 5.1K; R_0603_1608Metric
R4, R5: 22; R_0603_1608Metric
TP7: VBUS; TestPoint_Keystone_5019_Minature

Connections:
+5V: J4.T, J9.4, JP1.2 (B); also elsewhere on the board
/Battery Management/SCL: J4.R1, J9.3; also elsewhere on the board
/Battery Management/SDA: J4.R2, J9.2; also elsewhere on the board
/Controller/D+: J10.2, R5.2; also elsewhere on the board
/Controller/D-: J10.3, R4.2; also elsewhere on the board
GND: J4.S, J5.A1 (GND), J5.A12 (GND), J5.B1 (GND), J5.B12 (GND), J9.1, J10.1, R1.2, R2.1, R3.1; also elsewhere on the board
unnamed: J5.A5 (CC1), R3.2
unnamed: J5.A6 (D+), J5.B6 (D+), R5.1
unnamed: J5.A7 (D-), J5.B7 (D-), R4.1
unnamed: J5.B5 (CC2), R2.2
unnamed: J5.S1 (SHIELD), R1.1
VBUS: J5.A4 (VBUS), J5.A9 (VBUS), J5.B4 (VBUS), J5.B9 (VBUS), J10.4, JP1.1 (A), TP7.1; also elsewhere on the board

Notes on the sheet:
USB
TRRS
Rev 1 - Add test point to VBUS - Add jumper to bypass power ics for the other hand

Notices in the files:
README.md:
License:
General Code Copyright © 2015-2021 Matthew Adereth, Tom Short, and Joshua Shreve
Mini thumb cluster Copyright © 2015-2018 Matthew Adereth, Tom Short, and Leo Lou
Carbonfet thumb cluster © 2015-2018 Matthew Adereth, Tom Short, and carbonfet (github username)
The source code for generating the models (everything excluding the [things/](things/) and [resources/](resources/) directories is distributed under the [GNU AFFERO GENERAL PUBLIC LICENSE Version 3](LICENSE).  The generated models and PCB designs are distributed under the [Creative Commons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
